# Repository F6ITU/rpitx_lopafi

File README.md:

# rpitx_lopafi

Low pass filter for the Raspberry-Pi based TX RF transceiver

YAOHKP ! Yet another open hardware kicad project

LoPaFi is a "keep it simple stupid" version of a low pass filter with a Raspberry-Pi (or Up Board) form factor.

It is intended to fit on a RP Board running RpiTX by F5OEO

https://github.com/F5OEO/rpitx

This filter is made of 5 different Cauer filters with rejection notches on F2 and F3, using T50 toroids and 1206 smd caps

Switching is made with NEC EC2-5NU miniature relays (Kemet, NEC, Axicom), directly powered by the SoC board

Each relay is directly driven by a  bufferized and software driven GPIO

For more information, pse refer to the Wiki hosted on this very same wiki page
 
 This hardware development is "under construction" as long as a first version hasn't been "branched" 
 
 Please, do not fork before the first stable release unless you intend to contribute to the main development
 
 This project is protected by the CERN Open Hardware Licence https://www.ohwr.org/projects/cernohl/wiki

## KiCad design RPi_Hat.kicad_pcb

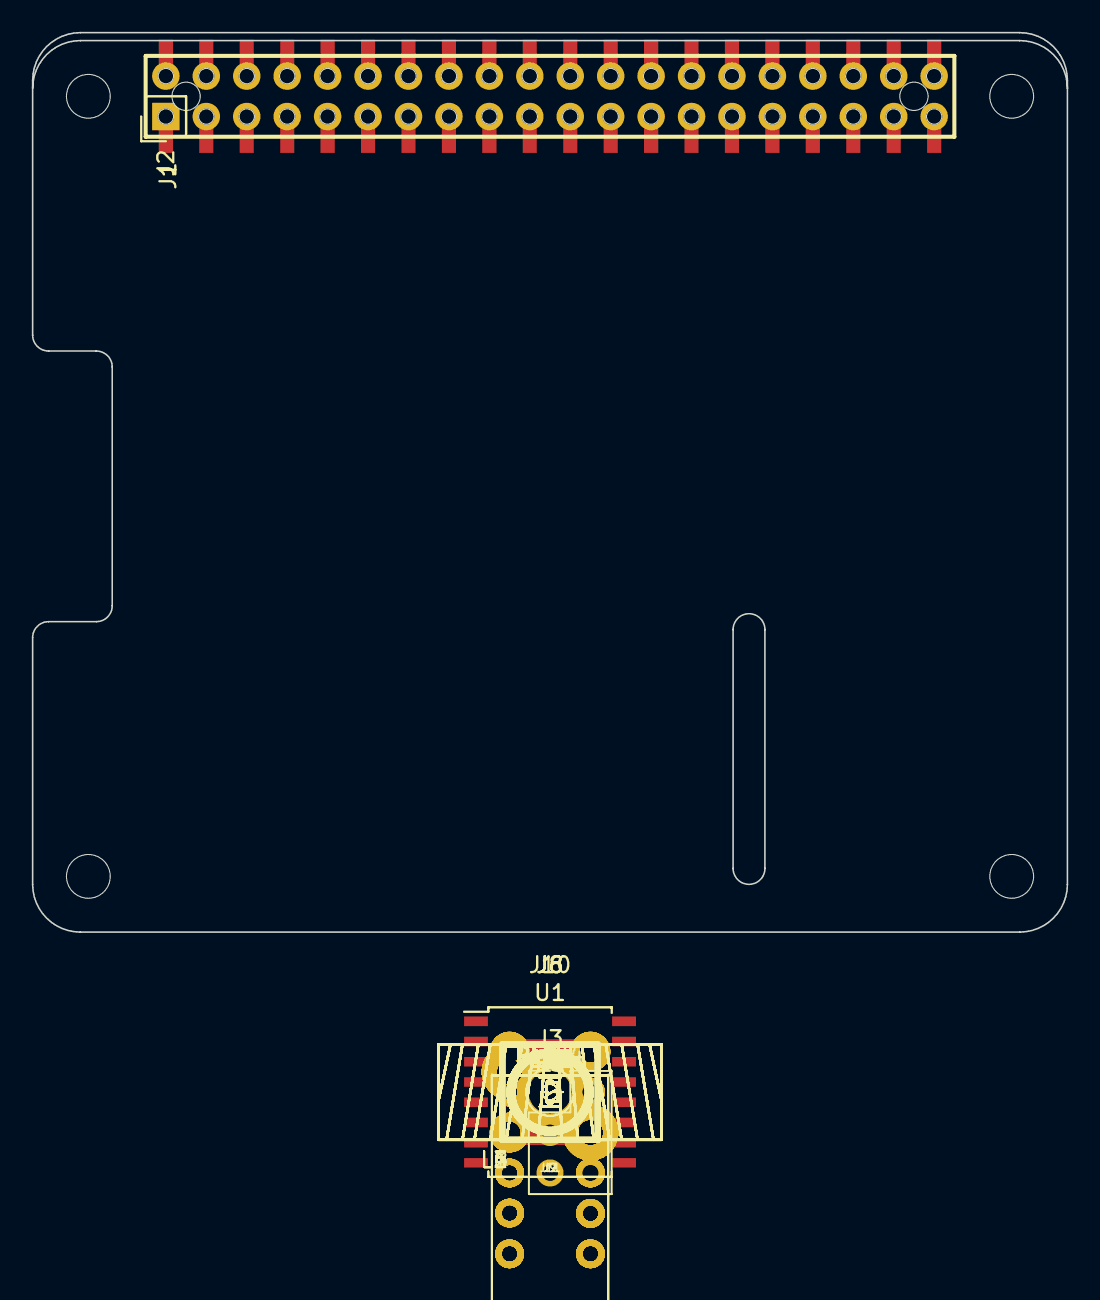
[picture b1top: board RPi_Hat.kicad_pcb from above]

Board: 2 copper layers, 65.0 x 56.5 mm, 51 parts (0 on the bottom side), 26 nets, no tracks yet.

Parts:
C1, C2, C3, C4, C5, C6, C7, C8, C9, C10, C11, C13, C14, C15, C16, C17, C18, C19, C20, C21, C22: C_Small; C_1206_3216Metric_Pad1.24x1.80mm_HandSolder
C12: 100n; C_1206_3216Metric_Pad1.24x1.80mm_HandSolder
J1: RPi_GPIO; Samtec_HLE-120-02-XXX-DV-BE-XX-XX
J2: Conn_01x01; Pin_Header_Straight_2x20
J3: Conn_01x01; MountingHole_2.7mm_M2.5_DIN965_Pad
J4: Conn_02x03_Odd_Even; PinHeader_2x03_P2.54mm_Vertical
J6, J8, J10: Conn_Coaxial; SMA_EDGE_NRW
J7, J9, J11: Conn_Coaxial; SMA_PINS
L1, L2, L3, L4, L5, L6: L_Small; T50_V_THT
R1, R2, R3, R4, R5, R6: 4k7; R_0805_2012Metric_Pad1.15x1.50mm_HandSolder
RL1, RL2, RL3, RL4, RL5, RL6: EC2-5NU; Relay_DPDT_NEC_EC2
U1: TCA9534; SOIC-16W_7.5x10.3mm_P1.27mm

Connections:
2.5MHz: RL1.12, RL2.12, U1.4
5V: C1.1, C2.2, C8.1, C9.2, C12.2, C16.1, C17.2, J4.1, J4.3, J4.5, R1.1, R2.1, R3.1, RL1.1, RL2.1, RL3.1, RL4.1, RL5.1, RL6.1, U1.16
6MHz: RL3.12, RL4.12, U1.5
12MHz: RL5.12, RL6.12, U1.6
GND: C1.2, C2.1, C5.2, C6.2, C7.2, C8.2, C9.1, C12.1, C13.2, C14.2, C15.2, C16.2, C17.1, C20.2, C21.2, C22.2, J2.1, J3.1, R4.2, R5.2, R6.2, RL1.3, RL1.10, RL2.3, RL2.10, RL3.3, RL3.10, RL4.3, RL4.10, RL5.3, RL5.10, RL6.3, RL6.10, U1.8
unnamed: C3.1, C4.2, C6.1, L1.2, L2.1
unnamed: C3.2, C5.1, L1.1, RL1.4, RL1.9
unnamed: C4.1, C7.1, L2.2, RL2.4, RL2.9
unnamed: C10.1, C11.2, C14.1, L3.2, L4.1
unnamed: C10.2, C13.1, L3.1, RL3.4, RL3.9
unnamed: C11.1, C15.1, L4.2, RL4.4, RL4.9
unnamed: C18.1, C19.2, C21.1, L5.2, L6.1
unnamed: C18.2, C20.1, L5.1, RL5.4, RL5.9
unnamed: C19.1, C22.1, L6.2, RL6.4, RL6.9
unnamed: J4.2, R4.1, U1.1
unnamed: J4.4, R5.1, U1.2
unnamed: J4.6, R6.1, U1.3
unnamed: J6.1, J7.1
unnamed: J6.2, J7.2
unnamed: J8.1, J9.1, RL1.5, RL1.8, RL3.5, RL3.8, RL5.5, RL5.8
unnamed: J8.2, J9.2
unnamed: J10.1, J11.1, RL2.5, RL2.8, RL4.5, RL4.8, RL6.5, RL6.8
unnamed: J10.2, J11.2
unnamed: R3.2, U1.13
SCL: R1.2, U1.14
SDA: R2.2, U1.15

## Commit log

2018-03-23 first commit, changes README
2018-03-24 first commit, first half-schematic
2018-03-25 first schematic
2018-04-01 whole schematic, first draft
